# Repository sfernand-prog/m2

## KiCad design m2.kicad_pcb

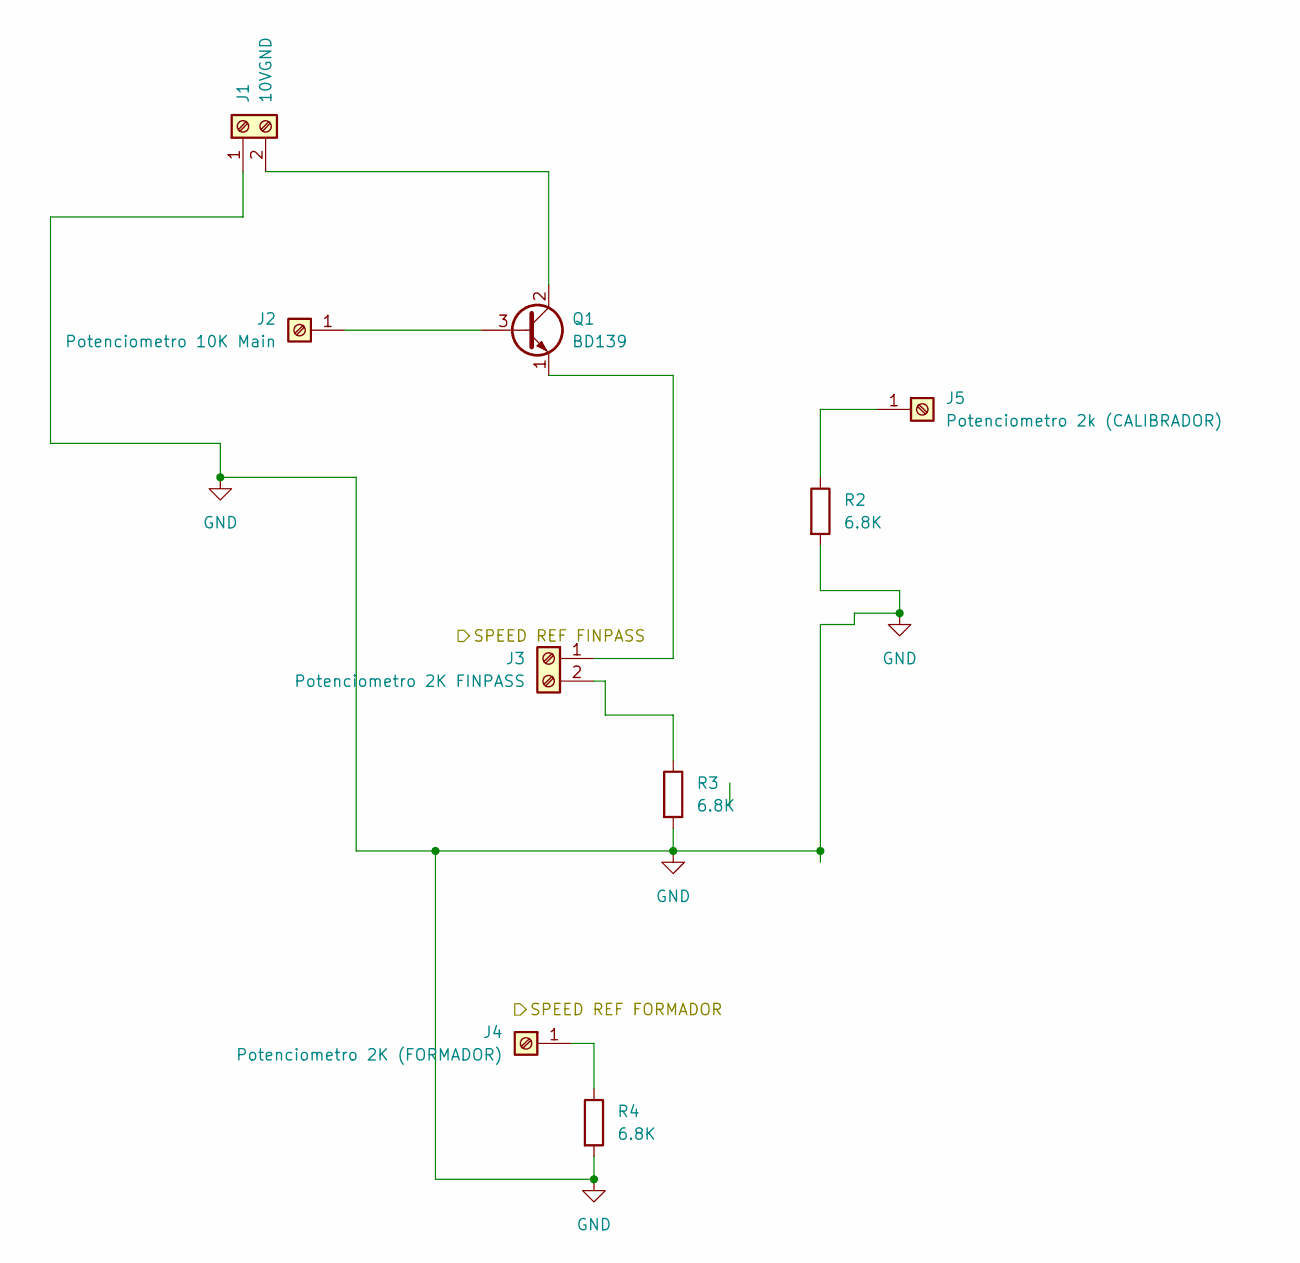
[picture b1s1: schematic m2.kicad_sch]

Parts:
J1: 10VGND; TerminalBlock_Phoenix_MKDS-1,5-2-5.08_1x02_P5.08mm_Horizont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
J2: Potenciometro 10K Main; SolderWire-0.1sqmm_1x01_D0.4mm_OD1mm
J3: Potenciometro 2K FINPASS; TerminalBlock_Phoenix_MKDS-1,5-2-5.08_1x02_P5.08mm_Horizont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
J4: Potenciometro 2K (FORMADOR); SolderWire-0.1sqmm_1x01_D0.4mm_OD1mm
J5: Potenciometro 2k (CALIBRADOR); SolderWire-0.1sqmm_1x01_D0.4mm_OD1mm
Q1: BD139; TO-126-3_Vertical
R2, R3, R4: 6.8K; R_Axial_DIN0207_L6.3mm_D2.5mm_P10.16mm_Horizontal

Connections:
GND: J1.1, R2.2, R3.2, R4.2
unnamed: J1.2, Q1.2 (C)
unnamed: J2.1, Q1.3 (B)
unnamed: J3.1, Q1.1 (E)
unnamed: J3.2, R3.1
unnamed: J4.1, R4.1
unnamed: J5.1, R2.1

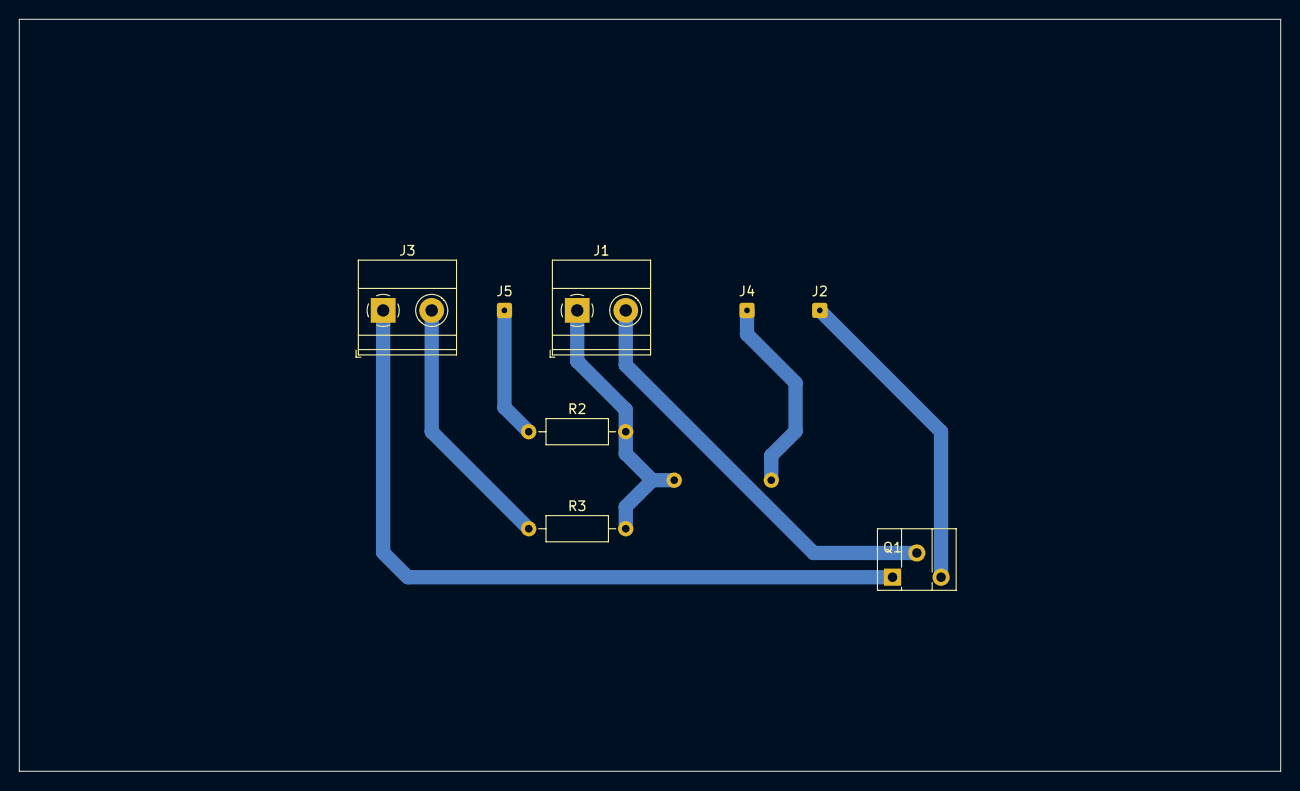
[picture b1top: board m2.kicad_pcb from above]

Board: 2 copper layers, 132.1 x 78.7 mm, 9 parts (1 on the bottom side), 7 nets.
